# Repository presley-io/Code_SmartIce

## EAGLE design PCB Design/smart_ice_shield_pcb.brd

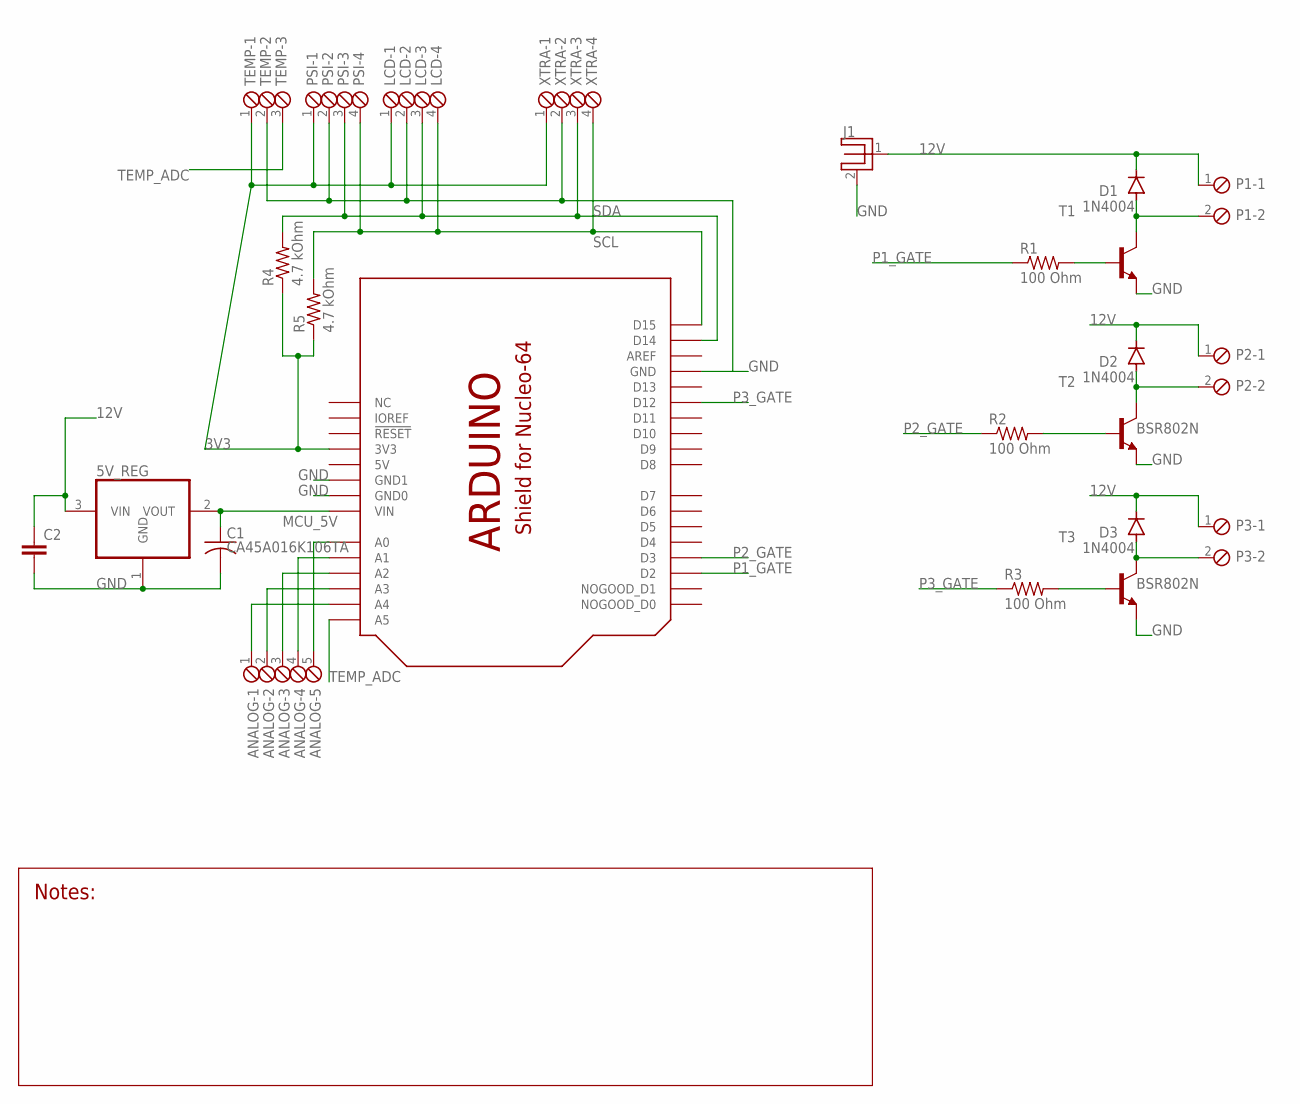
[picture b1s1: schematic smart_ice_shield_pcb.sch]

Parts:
5V_REG: LT1117CST; SOT223
ANALOG: SCREWTERM_5P_254; 5POL254
C1: CA45A016K106TA; C1206
C2: C-EU025-025X050; C025-025X050
D1, D2, D3: 1N4004; DO41-10
J1: BARREL5.5X2.1PJ-037A; PJ-037A
LCD: SCREWTERM_4P_254; 4POL254
P1, P2, P3: SCREWTERM_2P_381; 2POL381
PSI: SCREWTERM_4P_254; 4POL254
R1, R2, R3: 100 Ohm; R0805
R4, R5: 4.7 kOhm; R0805
T1, T2, T3: BSR802N; SOT23-BEC
TEMP: SCREWTERM_3P_254; 3POL254
U$1: SHIELD_FOR_NUCLE0_64_SHORT; SHIELD_FOR_NUCLEO_64_SHORT
XTRA: SCREWTERM_4P_254; 4POL254

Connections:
3V3: LCD.1, PSI.1, R4.1, R5.1, TEMP.1, U$1.3V (3V3), XTRA.1
5V: U$1.5V
12V: 5V_REG.3 (VIN), C2.1, D1.C, D2.C, D3.C, J1.1 (CENTER), P1.1, P2.1, P3.1
GATE: R1.2, T1.B
GATE1: R2.2, T2.B
GATE2: R3.2, T3.B
GND: 5V_REG.1 (GND), C1.2, C2.2, J1.2 (BARREL), LCD.2, PSI.2, T1.E, T2.E, T3.E, TEMP.2, U$1.GND, U$1.GND1 (GND0), U$1.GND2 (GND1), XTRA.2
M-: D1.A, P1.2, T1.C
M-1: D2.A, P2.2, T2.C
M-2: D3.A, P3.2, T3.C
MCU_5V: 5V_REG.2 (VOUT), C1.1, U$1.VIN
unnamed: ANALOG.5, U$1.A0
unnamed: ANALOG.4, U$1.A1
unnamed: ANALOG.3, U$1.A2
unnamed: ANALOG.2, U$1.A3
unnamed: ANALOG.1, U$1.A4
P1_GATE: R1.1, U$1.D2
P2_GATE: R2.1, U$1.D3
P3_GATE: R3.1, U$1.D12
SCL: LCD.4, PSI.4, R5.2, U$1.D15, XTRA.4
SDA: LCD.3, PSI.3, R4.2, U$1.D14, XTRA.3
TEMP_ADC: TEMP.3, U$1.A5

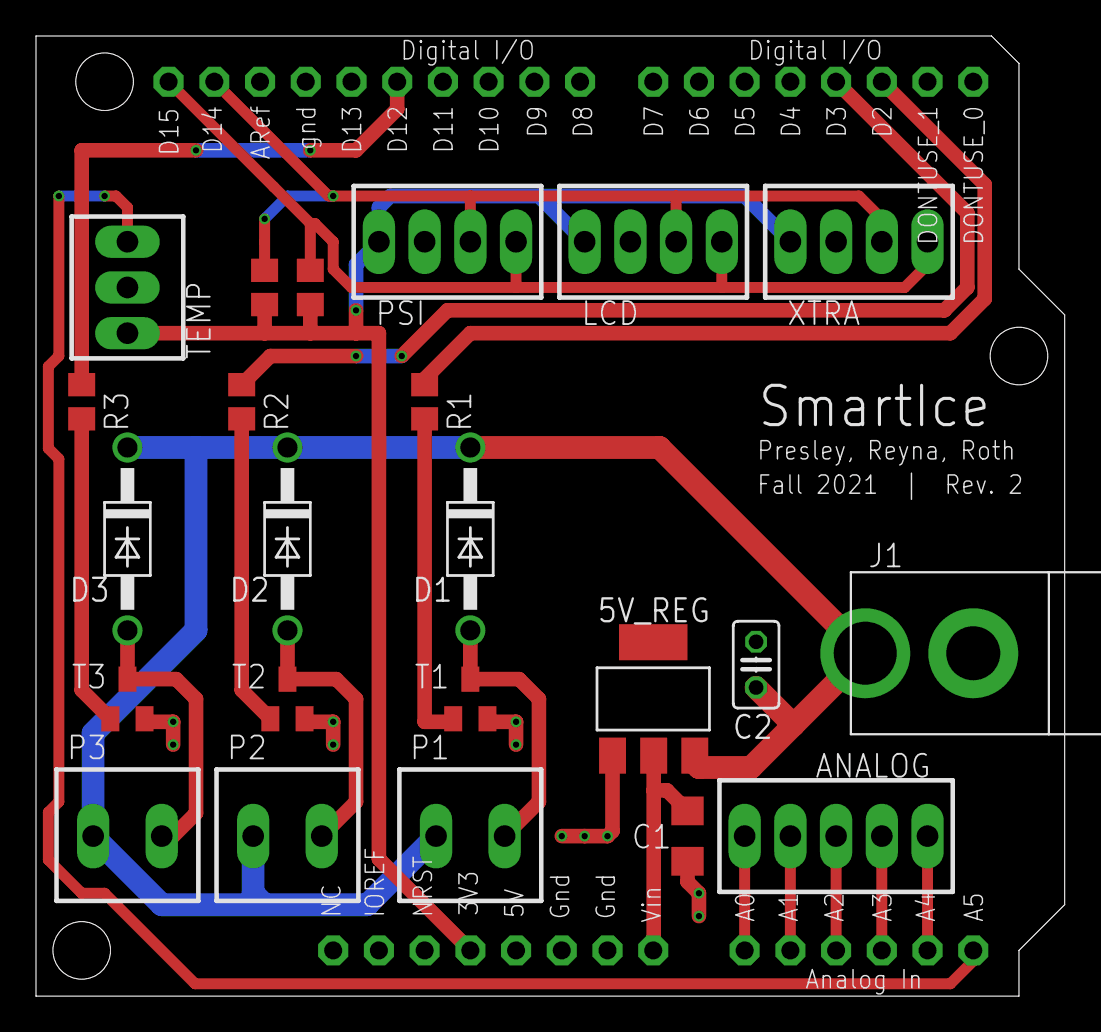
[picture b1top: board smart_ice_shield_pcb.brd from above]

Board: 2 copper layers, 57.1 x 53.3 mm, 24 parts (0 on the bottom side), 21 nets.

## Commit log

2021-12-07 General updates
    You know. Goodies.
2021-12-07 Lots of docs
    More docs bruh
2021-12-07 Even better docs
    Enjoy world
2021-12-07 Even better, better docs
    Enjoy pt2
2021-12-07 Board design files uploaded
2021-12-08 Parts list
    These links and quantities may be helpful for reordering this board!
